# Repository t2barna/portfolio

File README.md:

# portfolio
My projects from the university, unfortunately the documentations are in hungarian

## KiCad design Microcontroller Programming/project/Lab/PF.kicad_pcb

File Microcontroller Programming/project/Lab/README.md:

#PCB
This is the circuit design for the pcb for this project

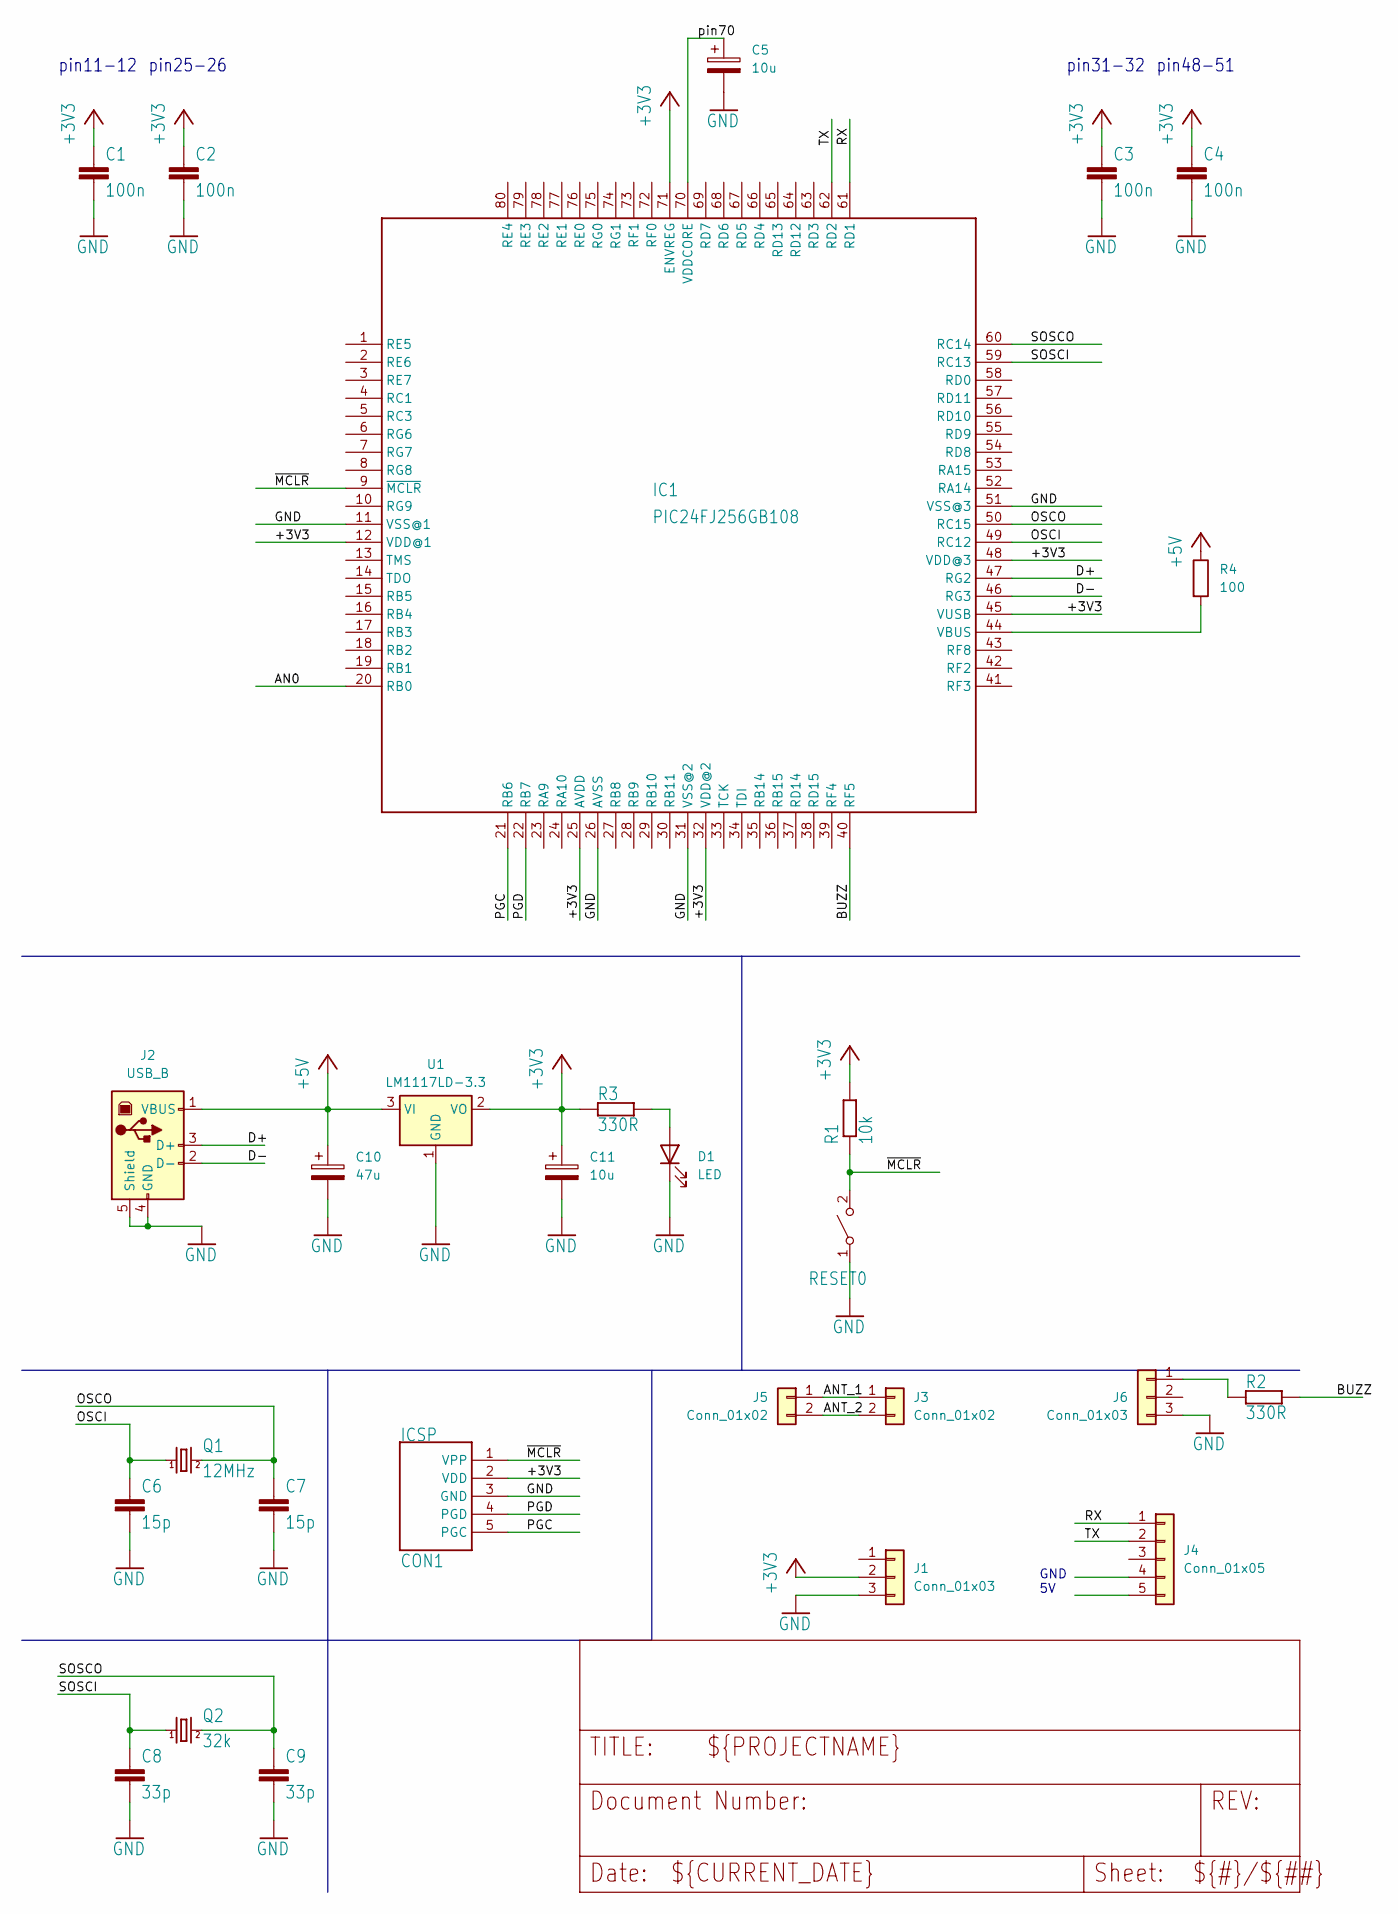
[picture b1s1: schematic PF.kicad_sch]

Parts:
C1, C2, C3, C4: 100n; C_0603_1608Metric
C5, C11: 10u; C_0603_1608Metric
C6, C7: 15p; C_0603_1608Metric
C8, C9: 33p; C_0603_1608Metric
C10: 47u; C_0603_1608Metric
CON1: ICSP; PinHeader_1x05_P2.54mm_Horizontal
D1: LED; LED_0603_1608Metric
IC1: PIC24FJ256GB108; TQFP80-12X12
J1, J6: Conn_01x03; PinSocket_1x03_P2.54mm_Vertical
J2: USB_B; USB_B_OST_USB-B1HSxx_Horizontal
J3: Conn_01x02; PinSocket_1x02_P2.54mm_Vertical
J4: Conn_01x05; PinSocket_1x05_P2.54mm_Vertical
J5: Conn_01x02; PinHeader_1x02_P2.54mm_Vertical
Q1: 12MHz; Crystal_HC49-U_Vertical
Q2: 32k; Crystal_DS26_D2.0mm_L6.0mm_Vertical
R1: 10k; R_1206_3216Metric
R2, R3: 330R; R_1206_3216Metric
R4: 100; R_1206_3216Metric
RESET0: 10-XX; SW_SPST_Omron_B3FS-100xP
U1: LM1117LD-3.3; SOT223

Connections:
+3V3: C1.1, C2.1, C3.1, C4.1, C11.1, CON1.2 (VDD), IC1.12 (VDD@1), IC1.25 (AVDD), IC1.32 (VDD@2), IC1.45 (VUSB), IC1.48 (VDD@3), IC1.71 (ENVREG), J1.2, R1.2, R3.2, U1.2 (VO)
+5V: C10.1, J2.1 (VBUS), R4.1, U1.3 (VI)
/AN0: IC1.20 (RB0)
/ANT_1: J3.1, J5.1
/ANT_2: J3.2, J5.2
/BUZZ: IC1.40 (RF5), R2.1
/D+: IC1.47 (RG2), J2.3 (D+)
/D-: IC1.46 (RG3), J2.2 (D-)
/OSCI: C6.1, IC1.49 (RC12), Q1.1
/OSCO: C7.1, IC1.50 (RC15), Q1.2
/PGC: CON1.5 (PGC), IC1.21 (RB6)
/PGD: CON1.4 (PGD), IC1.22 (RB7)
/RX: IC1.61 (RD1), J4.1
/SOSCI: C8.1, IC1.59 (RC13), Q2.1
/SOSCO: C9.1, IC1.60 (RC14), Q2.2
/TX: IC1.62 (RD2), J4.2
/pin70: C5.1, IC1.70 (VDDCORE)
/~MCLR: CON1.1 (VPP), IC1.9 (~MCLR), R1.1, RESET0.2 (B)
GND: C1.2, C2.2, C3.2, C4.2, C5.2, C6.2, C7.2, C8.2, C9.2, C10.2, C11.2, CON1.3 (GND), D1.1 (K), IC1.11 (VSS@1), IC1.26 (AVSS), IC1.31 (VSS@2), IC1.51 (VSS@3), J1.3, J2.4 (GND), J2.5 (Shield), J6.3, RESET0.1 (A), U1.1 (GND)
unnamed: D1.2 (A), R3.1
unnamed: IC1.44 (VBUS), R4.2
unnamed: J6.1, R2.2

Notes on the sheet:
GND 5V
pin48-51
pin31-32
pin11-12
pin25-26

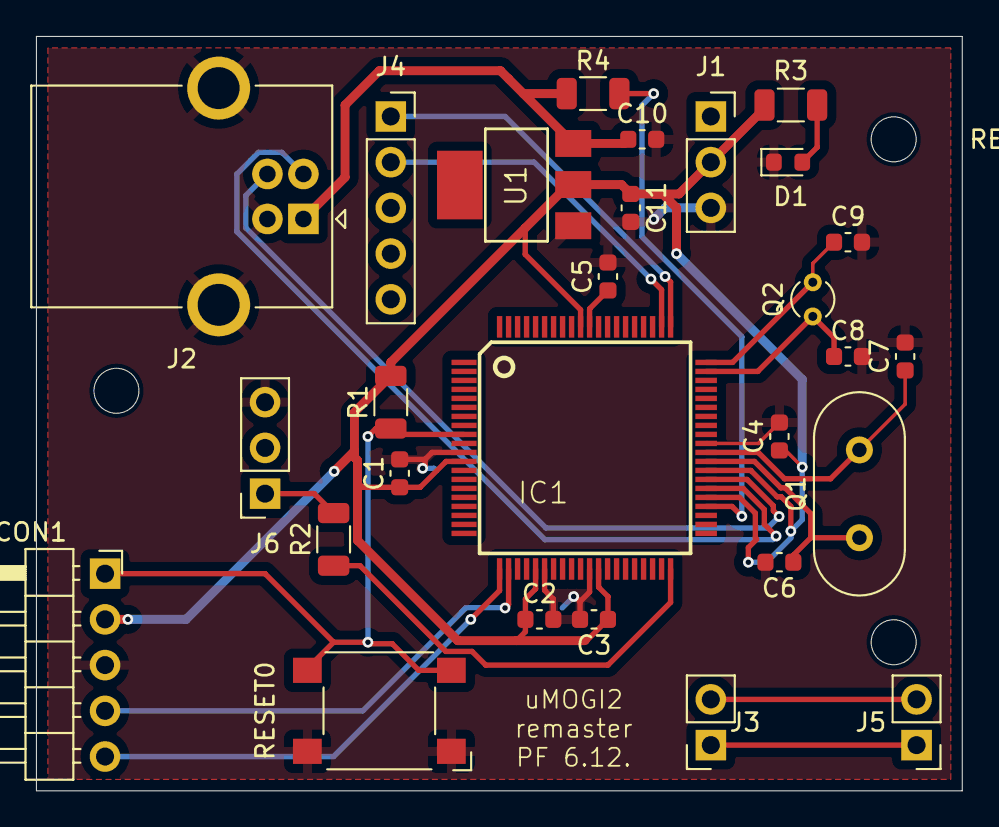
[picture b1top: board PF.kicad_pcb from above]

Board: 2 copper layers, 51.4 x 41.9 mm, 28 parts (0 on the bottom side), 21 nets.

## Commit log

2024-03-29 upload projects
2024-03-29 upload projectsupload projects
